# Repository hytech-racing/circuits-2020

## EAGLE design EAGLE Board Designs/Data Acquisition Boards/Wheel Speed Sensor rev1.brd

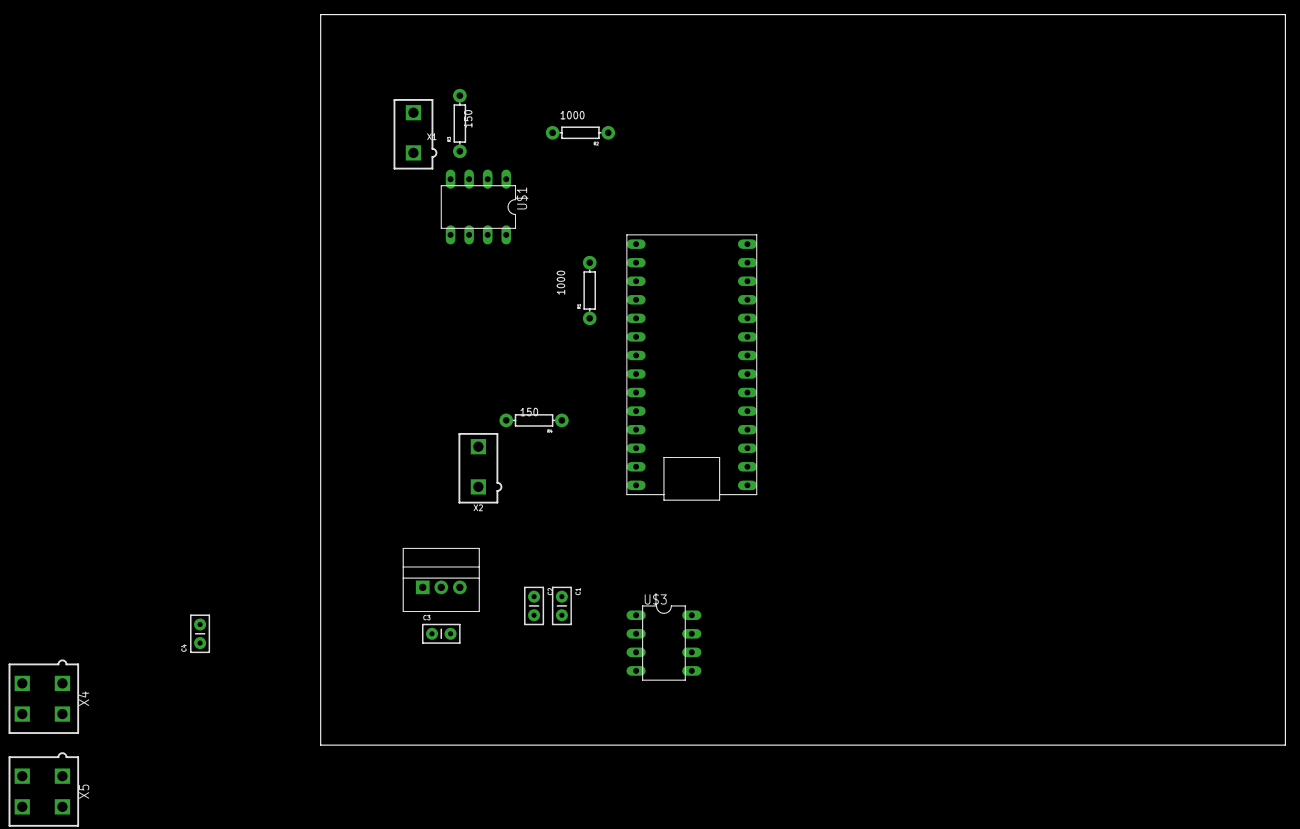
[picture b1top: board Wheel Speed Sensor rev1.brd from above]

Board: 2 copper layers, 132.1 x 100.0 mm, 16 parts (0 on the bottom side), 13 nets, no tracks yet.

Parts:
C1, C2: 1uF; CAP-PTH-SMALLEZ
C3, C4: CAP-PTH-SMALLEZ
R1, R2: 1000; AXIAL-0.3
R3, R4: 150; AXIAL-0.3
U$1: MCP6002PDIP; DIL08
U$2: TEENSY_3.2_SIMPLE
U$3: MCP2551DIL; DIL08
U$4: OKI-78SR-5; OKI-78SR
X1: Sensor 1; MINIFIT_5566-2
X2: Sensor 2; MINIFIT_5566-2
X4, X5: CONNECTOR-4; MINIFIT_5566-4

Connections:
3.3V: C1.2, C2.2, R1.P$1, U$1.8, U$2.3.3V, U$3.3
5V: C3.2, U$2.VIN, U$4.3
CANH: U$3.7, X4.3, X5.3
GND: C1.1, C2.1, C3.1, C4.1, R2.P$2, R3.P$2, R4.P$1, U$1.4, U$2.GND, U$3.2, U$3.8, U$4.2, X4.4, X5.4
unnamed: R1.P$2, R2.P$1, U$1.2, U$1.6
unnamed: U$3.6, X4.2, X5.2
unnamed: R3.P$1, U$1.3, X1.2
unnamed: U$1.7, U$2.A1
unnamed: U$1.1, U$2.D10(TX2)
unnamed: R4.P$2, U$1.5, X2.2
RX: U$2.A9, U$3.4
TX: U$2.A8, U$3.1
VIN: C4.2, U$4.1, X1.1, X2.1, X4.1, X5.1

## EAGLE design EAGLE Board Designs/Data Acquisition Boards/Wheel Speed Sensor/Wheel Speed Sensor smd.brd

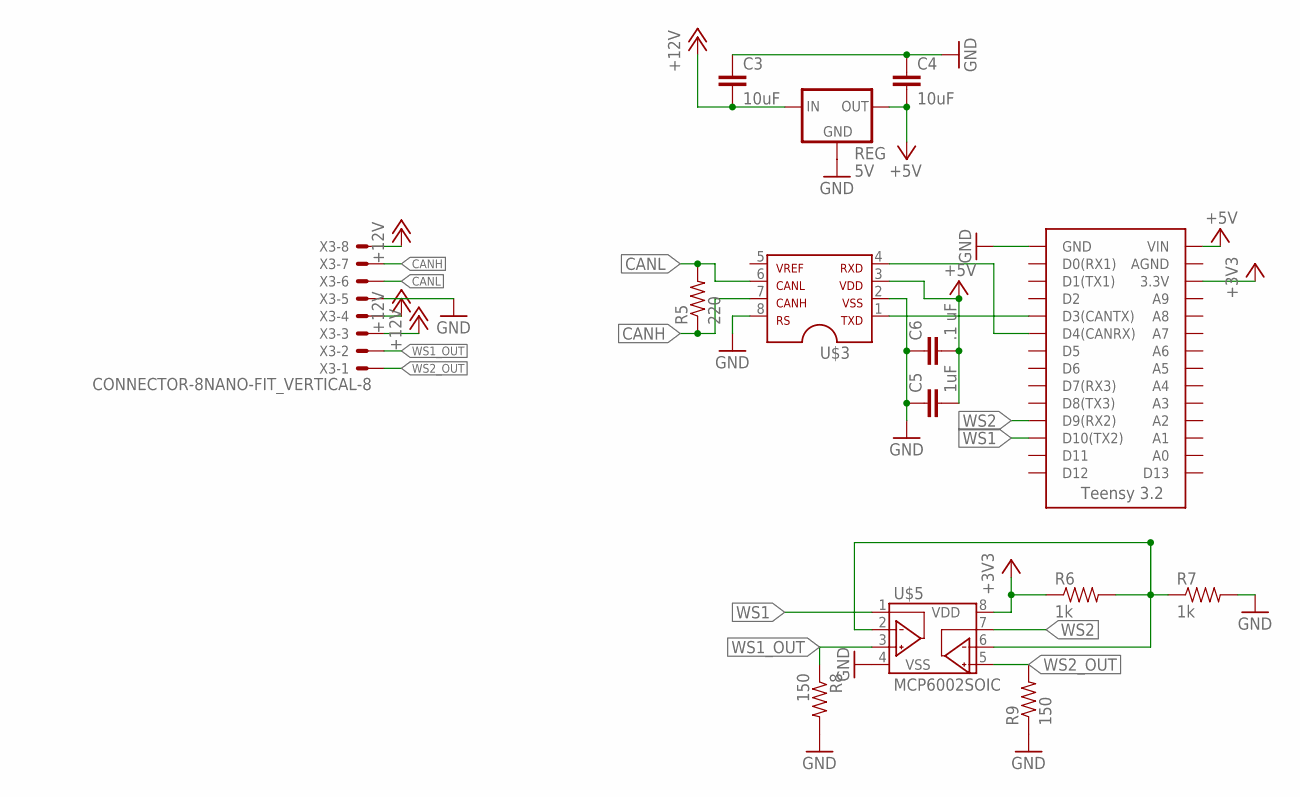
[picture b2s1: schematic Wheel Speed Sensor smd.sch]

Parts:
C3, C4: 10uF; 0603-CAP
C5: 1uF; 0603-CAP
C6: .1 uF; 0603-CAP
R5: 220; 0603-RES
R6, R7: 1k; 0603-RES
R8, R9: 150; 0603-RES
REG: 5V; OKI-78SR
U$2: TEENSY_3.2_SIMPLE
U$3: MCP2551; SOIC-08
U$5: MCP6002SOIC; SOIC-08
X3: CONNECTOR-8NANO-FIT_VERTICAL-8; NANO-FIT_VERTICAL-8

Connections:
+3V3: R6.1, U$2.3.3V, U$5.8 (VDD)
+5V: C4.2, C5.2, C6.2, REG.3 (OUT), U$2.VIN, U$3.3
+12V: C3.2, REG.1 (IN), X3.P$3, X3.P$4, X3.P$8
CANH: R5.1, U$3.7, X3.P$7
CANL: R5.2, U$3.6, X3.P$6
GND: C3.1, C4.1, C5.1, C6.1, R7.2, R8.2, R9.1, REG.2 (GND), U$2.GND, U$3.2, U$3.8, U$5.4 (VSS), X3.P$5
unnamed: U$2.D3(CANTX), U$3.1
unnamed: U$2.D4(CANRX), U$3.4
unnamed: R6.2, R7.1, U$5.2 (VINA-), U$5.6 (VINB-)
WS1: U$2.D10(TX2), U$5.1 (VOUTA)
WS1_OUT: R8.1, U$5.3 (VINA+), X3.P$2
WS2: U$2.D9(RX2), U$5.7 (VOUTB)
WS2_OUT: R9.2, U$5.5 (VINB+), X3.P$1

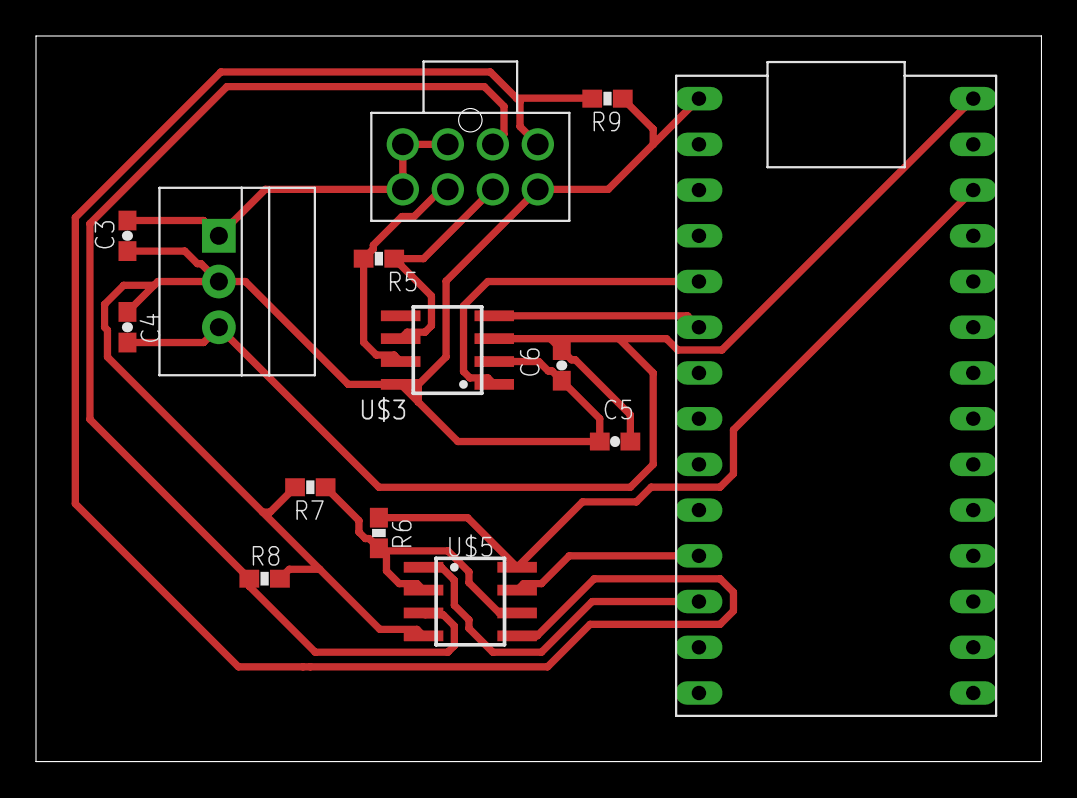
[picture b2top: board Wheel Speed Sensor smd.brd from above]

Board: 4 copper layers, 55.9 x 40.3 mm, 14 parts (0 on the bottom side), 13 nets.

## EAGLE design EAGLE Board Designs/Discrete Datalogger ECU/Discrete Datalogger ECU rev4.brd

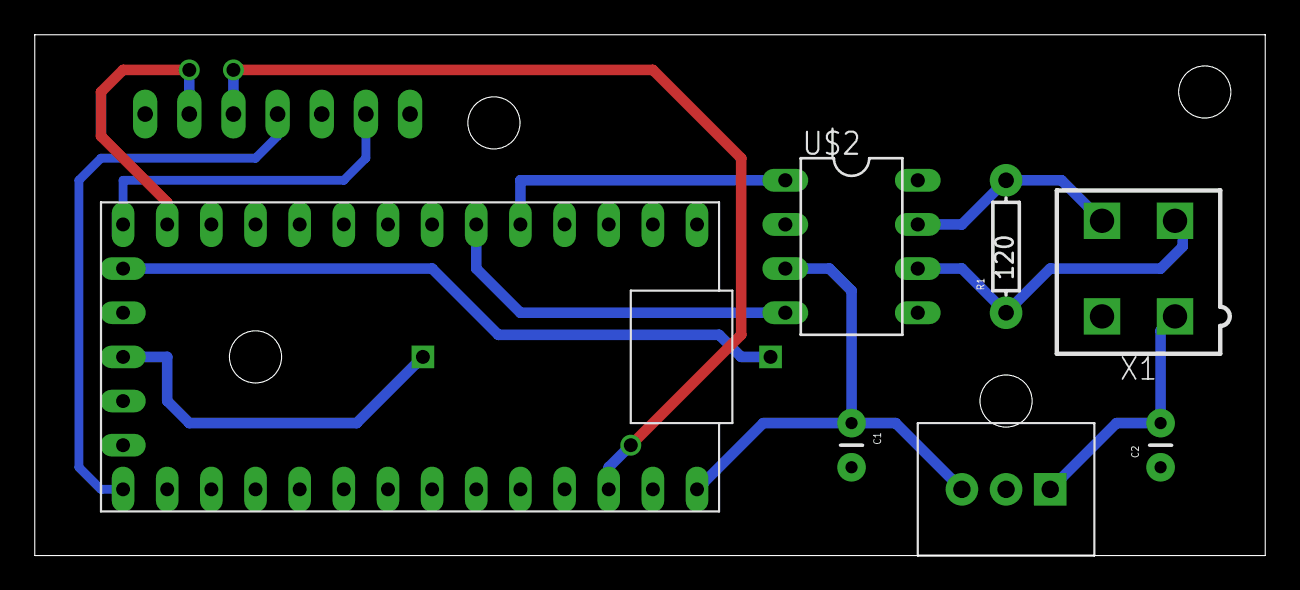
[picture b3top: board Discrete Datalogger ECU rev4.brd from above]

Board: 2 copper layers, 70.8 x 30.0 mm, 9 parts (1 on the bottom side), 13 nets.

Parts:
C1: 0.1uF; CAP-PTH-SMALL
C2: 0.33uF; CAP-PTH-SMALL
IC1: TO-220
R1: 120; AXIAL-0.3
U$1: TEENSY_3.2_EXT
U$2: MCP2551DIL; DIL08
U$3: SDCARD_INTERFACE
U$4: COIN-CELL-HOLDER
X1: CONNECTOR-4; MINIFIT_5566-4

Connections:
12V: C2.2, IC1.1, X1.1
CANH: R1.P$2, U$2.7, X1.4
CANL: R1.P$1, U$2.6, X1.3
GND: C1.2, C2.1, IC1.2, U$1.GND, U$2.2, U$2.8, U$3.CS, U$3.GND, X1.2
unnamed: U$1.VBAT, U$4.VDD
unnamed: U$1.GND2, U$4.GND
unnamed: U$1.D3(CANTX), U$2.1
unnamed: U$1.D4(CANRX), U$2.4
unnamed: U$1.D13, U$3.SCK
unnamed: U$1.D11, U$3.DI
unnamed: U$1.3.3V, U$3.VCC
unnamed: U$1.D12, U$3.DO
VIN: C1.1, IC1.3, U$1.VIN, U$2.3
